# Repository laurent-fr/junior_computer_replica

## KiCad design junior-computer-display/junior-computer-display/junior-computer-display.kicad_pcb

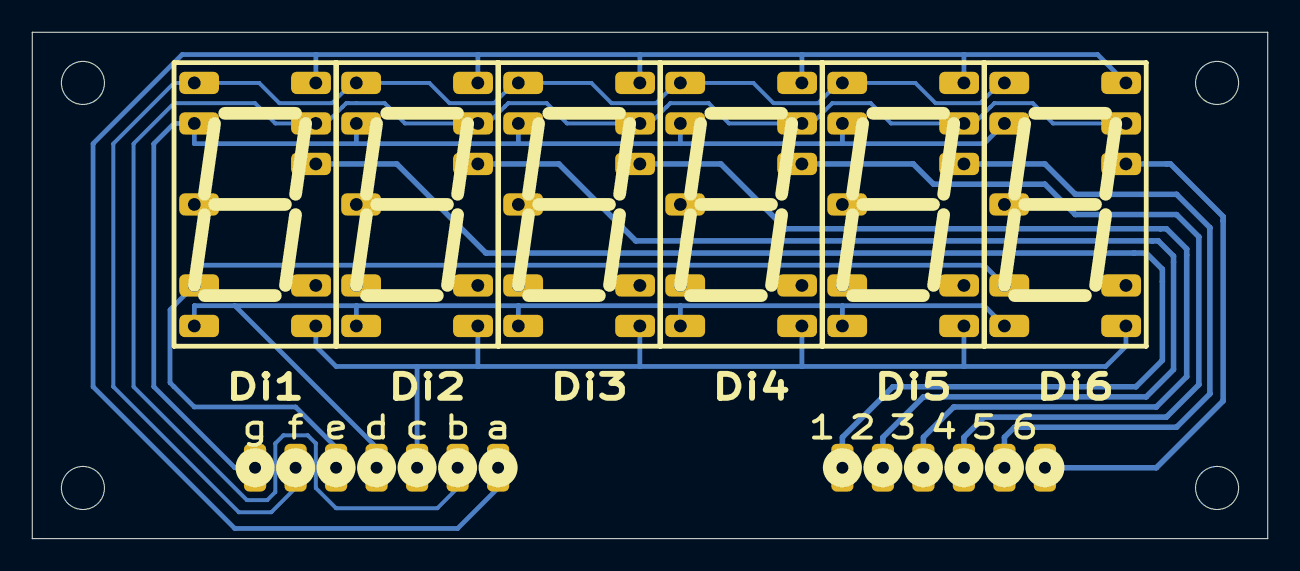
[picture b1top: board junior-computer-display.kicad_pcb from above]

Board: 2 copper layers, 77.5 x 31.8 mm, 7 parts (0 on the bottom side), 13 nets.

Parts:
Di1, Di2, Di3, Di4, Di5, Di6: MAN4640A; 7SEGMENT
J1: Display; Conn-Display-Top

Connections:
/X0: Di1.14, Di2.14, Di3.14, Di4.14, Di5.14, Di6.14, J1.a
/X1: Di1.13, Di2.13, Di3.13, Di4.13, Di5.13, Di6.13, J1.b
/X2: Di1.8, Di2.8, Di3.8, Di4.8, Di5.8, Di6.8, J1.c
/X3: Di1.7, Di2.7, Di3.7, Di4.7, Di5.7, Di6.7, J1.d
/X4: Di1.6, Di2.6, Di3.6, Di4.6, Di5.6, Di6.6, J1.e
/X5: Di1.1, Di2.1, Di3.1, Di4.1, Di5.1, Di6.1, J1.f
/X6: Di1.2, Di2.2, Di3.2, Di4.2, Di5.2, Di6.2, J1.g
unnamed: Di1.4, Di1.12, J1.1
unnamed: Di2.4, Di2.12, J1.2
unnamed: Di3.4, Di3.12, J1.3
unnamed: Di4.4, Di4.12, J1.4
unnamed: Di5.4, Di5.12, J1.5
unnamed: Di6.4, Di6.12, J1.6
